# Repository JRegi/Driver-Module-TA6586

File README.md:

# Dual Driver Module with TA6586

## **Description**
A little module with two TA6586 full-bridge drivers, designed to be small while maintaining a decent thermal performance.
The PCB is designed for PCBWay Quick-Turn PCB capabilities.

# 3D view

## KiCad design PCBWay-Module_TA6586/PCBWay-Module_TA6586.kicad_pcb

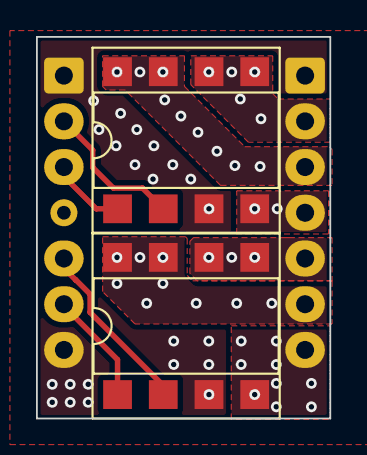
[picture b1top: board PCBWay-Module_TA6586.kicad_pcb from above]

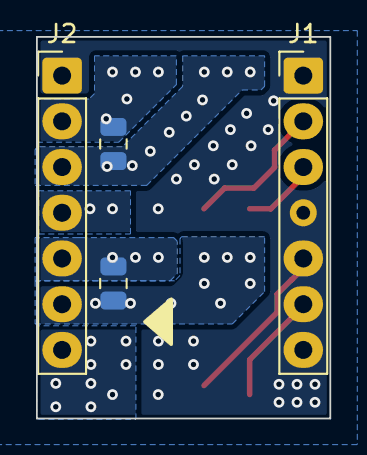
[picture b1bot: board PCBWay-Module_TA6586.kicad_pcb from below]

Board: 2 copper layers, 16.3 x 21.2 mm, 6 parts (4 on the bottom side), 10 nets.

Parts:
C1, C2: 100; C_0805_2012Metric
J1, J2: Conn_01x07_Pin; PinHeader_1x07_P2.54mm_Vertical
U1, U2: DIP-8_W7.62mm_SMDSocket_SmallPads

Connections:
/IN_A1: J1.6, U1.1 (IN1)
/IN_A2: J1.5, U1.2 (IN2)
/IN_B1: J1.3, U2.1 (IN1)
/IN_B2: J1.2, U2.2 (IN2)
/OUT_A1: C2.2, J2.5, U1.5 (OUT1), U1.6 (OUT1)
/OUT_A2: C2.1, J2.6, U1.7 (OUT2), U1.8 (OUT2)
/OUT_B1: C1.2, J2.2, U2.5 (OUT1), U2.6 (OUT1)
/OUT_B2: C1.1, J2.3, U2.7 (OUT2), U2.8 (OUT2)
/VM: J2.4, J2.7, U1.4 (VM), U2.4 (VM)
GND: J1.1, J1.7, J2.1, U1.3 (GND), U2.3 (GND)

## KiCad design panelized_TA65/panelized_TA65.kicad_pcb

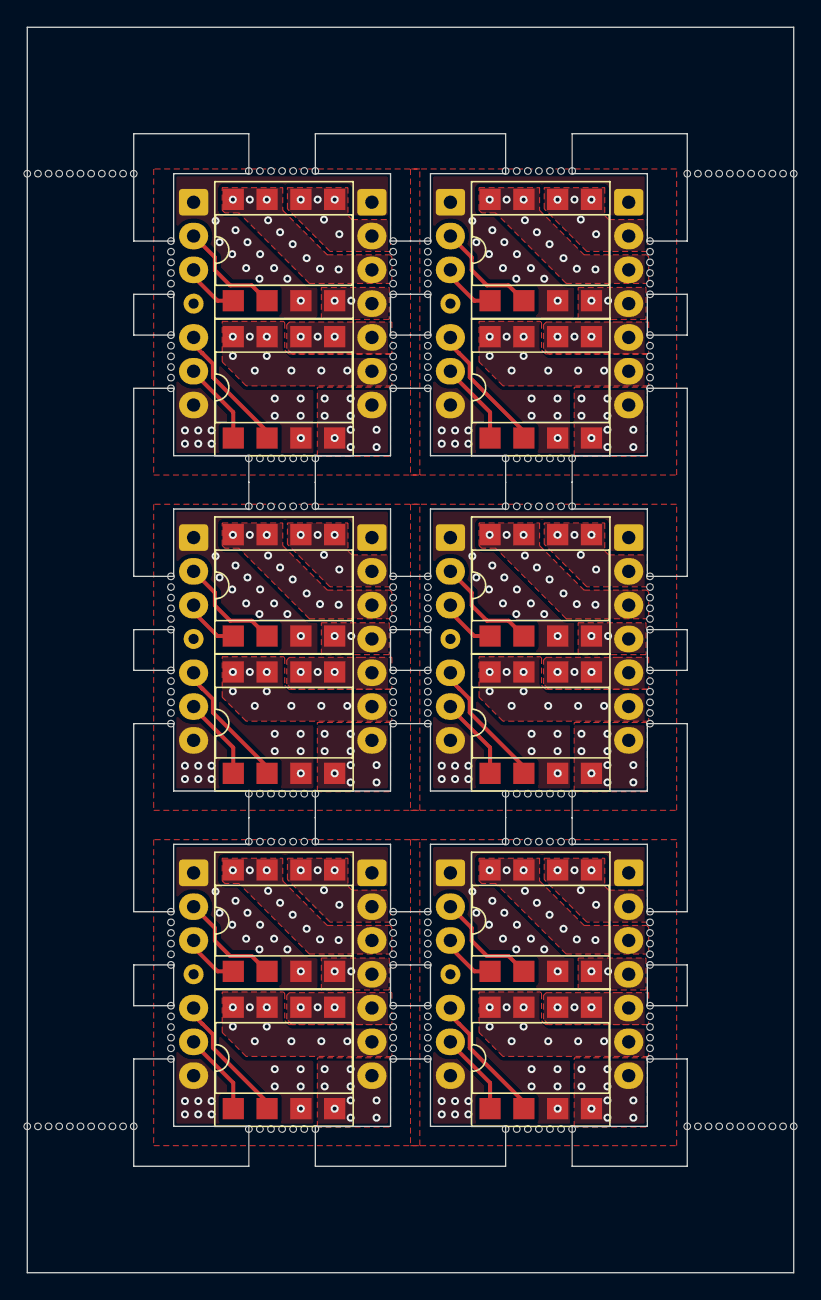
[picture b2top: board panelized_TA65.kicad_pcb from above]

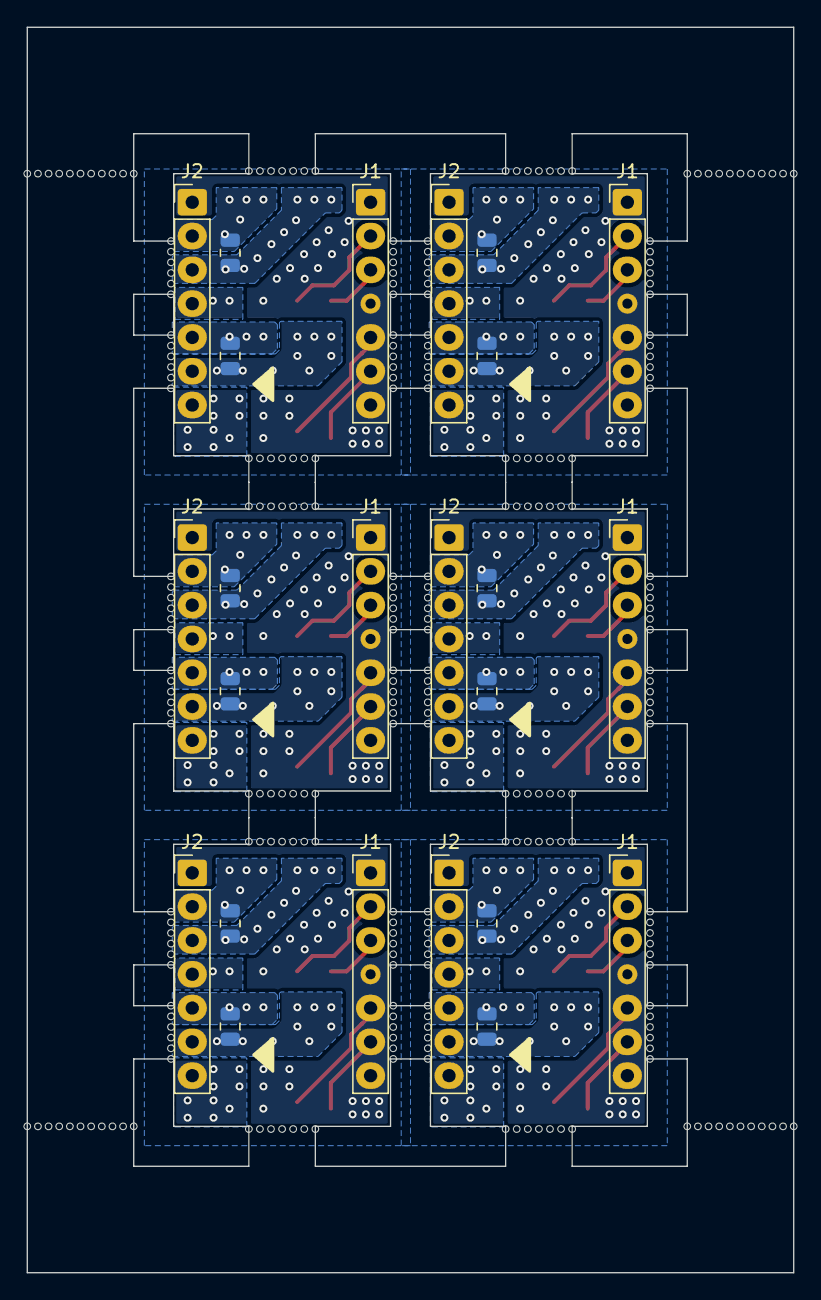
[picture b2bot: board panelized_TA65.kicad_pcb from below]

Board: 2 copper layers, 57.6 x 93.6 mm, 308 parts (24 on the bottom side), 60 nets.

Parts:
C1, C1#2, C1#3, C1#4, C1#5, C1#6, C2, C2#2, C2#3, C2#4, C2#5, C2#6: 100; C_0805_2012Metric
J1, J1#2, J1#3, J1#4, J1#5, J1#6, J2, J2#2, J2#3, J2#4, J2#5, J2#6: Conn_01x07_Pin; PinHeader_1x07_P2.54mm_Vertical
KiKit_MB_1_1, KiKit_MB_1_2, KiKit_MB_1_3, KiKit_MB_1_4, KiKit_MB_1_5, KiKit_MB_1_6, KiKit_MB_2_1, KiKit_MB_2_2, KiKit_MB_2_3, KiKit_MB_2_4, KiKit_MB_2_5, KiKit_MB_2_6, KiKit_MB_3_1, KiKit_MB_3_2, KiKit_MB_3_3, KiKit_MB_3_4, KiKit_MB_3_5, KiKit_MB_3_6, KiKit_MB_4_1, KiKit_MB_4_2, KiKit_MB_4_3, KiKit_MB_4_4, KiKit_MB_4_5, KiKit_MB_4_6, KiKit_MB_5_1, KiKit_MB_5_2, KiKit_MB_5_3, KiKit_MB_5_4, KiKit_MB_5_5, KiKit_MB_5_6, KiKit_MB_5_7, KiKit_MB_6_1, KiKit_MB_6_2, KiKit_MB_6_3, KiKit_MB_6_4, KiKit_MB_6_5, KiKit_MB_6_6, KiKit_MB_6_7, KiKit_MB_7_1, KiKit_MB_7_2, KiKit_MB_7_3, KiKit_MB_7_4, KiKit_MB_7_5, KiKit_MB_7_6, KiKit_MB_8_1, KiKit_MB_8_2, KiKit_MB_8_3, KiKit_MB_8_4, KiKit_MB_8_5, KiKit_MB_8_6, KiKit_MB_9_1, KiKit_MB_9_2, KiKit_MB_9_3, KiKit_MB_9_4, KiKit_MB_9_5, KiKit_MB_9_6, KiKit_MB_10_1, KiKit_MB_10_2, KiKit_MB_10_3, KiKit_MB_10_4, KiKit_MB_10_5, KiKit_MB_10_6, KiKit_MB_11_1, KiKit_MB_11_2, KiKit_MB_11_3, KiKit_MB_11_4, KiKit_MB_11_5, KiKit_MB_11_6, KiKit_MB_11_7, KiKit_MB_12_1, KiKit_MB_12_2, KiKit_MB_12_3, KiKit_MB_12_4, KiKit_MB_12_5, KiKit_MB_12_6, KiKit_MB_12_7, KiKit_MB_13_1, KiKit_MB_13_2, KiKit_MB_13_3, KiKit_MB_13_4, KiKit_MB_13_5, KiKit_MB_13_6, KiKit_MB_14_1, KiKit_MB_14_2, KiKit_MB_14_3, KiKit_MB_14_4, KiKit_MB_14_5, KiKit_MB_14_6, KiKit_MB_15_1, KiKit_MB_15_2, KiKit_MB_15_3, KiKit_MB_15_4, KiKit_MB_15_5, KiKit_MB_15_6, KiKit_MB_16_1, KiKit_MB_16_2, KiKit_MB_16_3, KiKit_MB_16_4, KiKit_MB_16_5, KiKit_MB_16_6, KiKit_MB_17_1, KiKit_MB_17_2, KiKit_MB_17_3, KiKit_MB_17_4, KiKit_MB_17_5, KiKit_MB_17_6, KiKit_MB_17_7, KiKit_MB_18_1, KiKit_MB_18_2, KiKit_MB_18_3, KiKit_MB_18_4, KiKit_MB_18_5, KiKit_MB_18_6, KiKit_MB_18_7, KiKit_MB_19_1, KiKit_MB_19_2, KiKit_MB_19_3, KiKit_MB_19_4, KiKit_MB_19_5, KiKit_MB_19_6, KiKit_MB_20_1, KiKit_MB_20_2, KiKit_MB_20_3, KiKit_MB_20_4, KiKit_MB_20_5, KiKit_MB_20_6, KiKit_MB_21_1, KiKit_MB_21_2, KiKit_MB_21_3, KiKit_MB_21_4, KiKit_MB_21_5, KiKit_MB_21_6, KiKit_MB_22_1, KiKit_MB_22_2, KiKit_MB_22_3, KiKit_MB_22_4, KiKit_MB_22_5, KiKit_MB_22_6, KiKit_MB_23_1, KiKit_MB_23_2, KiKit_MB_23_3, KiKit_MB_23_4, KiKit_MB_23_5, KiKit_MB_23_6, KiKit_MB_23_7, KiKit_MB_24_1, KiKit_MB_24_2, KiKit_MB_24_3, KiKit_MB_24_4, KiKit_MB_24_5, KiKit_MB_24_6, KiKit_MB_24_7, KiKit_MB_25_1, KiKit_MB_25_2, KiKit_MB_25_3, KiKit_MB_25_4, KiKit_MB_25_5, KiKit_MB_25_6, KiKit_MB_26_1, KiKit_MB_26_2, KiKit_MB_26_3, KiKit_MB_26_4, KiKit_MB_26_5, KiKit_MB_26_6, KiKit_MB_27_1, KiKit_MB_27_2, KiKit_MB_27_3, KiKit_MB_27_4, KiKit_MB_27_5, KiKit_MB_27_6, KiKit_MB_28_1, KiKit_MB_28_2, KiKit_MB_28_3, KiKit_MB_28_4, KiKit_MB_28_5, KiKit_MB_28_6, KiKit_MB_29_1, KiKit_MB_29_2, KiKit_MB_29_3, KiKit_MB_29_4, KiKit_MB_29_5, KiKit_MB_29_6, KiKit_MB_29_7, KiKit_MB_30_1, KiKit_MB_30_2, KiKit_MB_30_3, KiKit_MB_30_4, KiKit_MB_30_5, KiKit_MB_30_6, KiKit_MB_30_7, KiKit_MB_31_1, KiKit_MB_31_2, KiKit_MB_31_3, KiKit_MB_31_4, KiKit_MB_31_5, KiKit_MB_31_6, KiKit_MB_32_1, KiKit_MB_32_2, KiKit_MB_32_3, KiKit_MB_32_4, KiKit_MB_32_5, KiKit_MB_32_6, KiKit_MB_33_1, KiKit_MB_33_2, KiKit_MB_33_3, KiKit_MB_33_4, KiKit_MB_33_5, KiKit_MB_33_6, KiKit_MB_34_1, KiKit_MB_34_2, KiKit_MB_34_3, KiKit_MB_34_4, KiKit_MB_34_5, KiKit_MB_34_6, KiKit_MB_35_1, KiKit_MB_35_2, KiKit_MB_35_3, KiKit_MB_35_4, KiKit_MB_35_5, KiKit_MB_35_6, KiKit_MB_35_7, KiKit_MB_36_1, KiKit_MB_36_2, KiKit_MB_36_3, KiKit_MB_36_4, KiKit_MB_36_5, KiKit_MB_36_6, KiKit_MB_36_7, KiKit_MB_37_1, KiKit_MB_37_2, KiKit_MB_37_3, KiKit_MB_37_4, KiKit_MB_37_5, KiKit_MB_37_6, KiKit_MB_37_7, KiKit_MB_37_8, KiKit_MB_37_9, KiKit_MB_37_10, KiKit_MB_37_11, KiKit_MB_38_1, KiKit_MB_38_2, KiKit_MB_38_3, KiKit_MB_38_4, KiKit_MB_38_5, KiKit_MB_38_6, KiKit_MB_38_7, KiKit_MB_38_8, KiKit_MB_38_9, KiKit_MB_38_10, KiKit_MB_38_11, KiKit_MB_39_1, KiKit_MB_39_2, KiKit_MB_39_3, KiKit_MB_39_4, KiKit_MB_39_5, KiKit_MB_39_6, KiKit_MB_39_7, KiKit_MB_39_8, KiKit_MB_39_9, KiKit_MB_39_10, KiKit_MB_39_11, KiKit_MB_40_1, KiKit_MB_40_2, KiKit_MB_40_3, KiKit_MB_40_4, KiKit_MB_40_5, KiKit_MB_40_6, KiKit_MB_40_7, KiKit_MB_40_8, KiKit_MB_40_9, KiKit_MB_40_10, KiKit_MB_40_11: NPTH
U1, U1#2, U1#3, U1#4, U1#5, U1#6, U2, U2#2, U2#3, U2#4, U2#5, U2#6: DIP-8_W7.62mm_SMDSocket_SmallPads

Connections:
Board_0-/IN_A1: J1#6.6, U1#4.1 (IN1)
Board_0-/IN_A2: J1#6.5, U1#4.2 (IN2)
Board_0-/IN_B1: J1#6.3, U2#3.1 (IN1)
Board_0-/IN_B2: J1#6.2, U2#3.2 (IN2)
Board_0-/OUT_A1: C2#3.2, J2.5, U1#4.5 (OUT1), U1#4.6 (OUT1)
Board_0-/OUT_A2: C2#3.1, J2.6, U1#4.7 (OUT2), U1#4.8 (OUT2)
Board_0-/OUT_B1: C1#4.2, J2.2, U2#3.5 (OUT1), U2#3.6 (OUT1)
Board_0-/OUT_B2: C1#4.1, J2.3, U2#3.7 (OUT2), U2#3.8 (OUT2)
Board_0-/VM: J2.4, J2.7, U1#4.4 (VM), U2#3.4 (VM)
Board_0-GND: J1#6.1, J1#6.7, J2.1, U1#4.3 (GND), U2#3.3 (GND)
Board_1-/IN_A1: J1#4.6, U1#3.1 (IN1)
Board_1-/IN_A2: J1#4.5, U1#3.2 (IN2)
Board_1-/IN_B1: J1#4.3, U2.1 (IN1)
Board_1-/IN_B2: J1#4.2, U2.2 (IN2)
Board_1-/OUT_A1: C2#2.2, J2#3.5, U1#3.5 (OUT1), U1#3.6 (OUT1)
Board_1-/OUT_A2: C2#2.1, J2#3.6, U1#3.7 (OUT2), U1#3.8 (OUT2)
Board_1-/OUT_B1: C1#3.2, J2#3.2, U2.5 (OUT1), U2.6 (OUT1)
Board_1-/OUT_B2: C1#3.1, J2#3.3, U2.7 (OUT2), U2.8 (OUT2)
Board_1-/VM: J2#3.4, J2#3.7, U1#3.4 (VM), U2.4 (VM)
Board_1-GND: J1#4.1, J1#4.7, J2#3.1, U1#3.3 (GND), U2.3 (GND)
Board_2-/IN_A1: J1#3.6, U1#5.1 (IN1)
Board_2-/IN_A2: J1#3.5, U1#5.2 (IN2)
Board_2-/IN_B1: J1#3.3, U2#2.1 (IN1)
Board_2-/IN_B2: J1#3.2, U2#2.2 (IN2)
Board_2-/OUT_A1: C2#4.2, J2#5.5, U1#5.5 (OUT1), U1#5.6 (OUT1)
Board_2-/OUT_A2: C2#4.1, J2#5.6, U1#5.7 (OUT2), U1#5.8 (OUT2)
Board_2-/OUT_B1: C1#2.2, J2#5.2, U2#2.5 (OUT1), U2#2.6 (OUT1)
Board_2-/OUT_B2: C1#2.1, J2#5.3, U2#2.7 (OUT2), U2#2.8 (OUT2)
Board_2-/VM: J2#5.4, J2#5.7, U1#5.4 (VM), U2#2.4 (VM)
Board_2-GND: J1#3.1, J1#3.7, J2#5.1, U1#5.3 (GND), U2#2.3 (GND)
Board_3-/IN_A1: J1#5.6, U1#6.1 (IN1)
Board_3-/IN_A2: J1#5.5, U1#6.2 (IN2)
Board_3-/IN_B1: J1#5.3, U2#5.1 (IN1)
Board_3-/IN_B2: J1#5.2, U2#5.2 (IN2)
Board_3-/OUT_A1: C2#5.2, J2#6.5, U1#6.5 (OUT1), U1#6.6 (OUT1)
Board_3-/OUT_A2: C2#5.1, J2#6.6, U1#6.7 (OUT2), U1#6.8 (OUT2)
Board_3-/OUT_B1: C1#6.2, J2#6.2, U2#5.5 (OUT1), U2#5.6 (OUT1)
Board_3-/OUT_B2: C1#6.1, J2#6.3, U2#5.7 (OUT2), U2#5.8 (OUT2)
Board_3-/VM: J2#6.4, J2#6.7, U1#6.4 (VM), U2#5.4 (VM)
Board_3-GND: J1#5.1, J1#5.7, J2#6.1, U1#6.3 (GND), U2#5.3 (GND)
Board_4-/IN_A1: J1.6, U1.1 (IN1)
Board_4-/IN_A2: J1.5, U1.2 (IN2)
Board_4-/IN_B1: J1.3, U2#6.1 (IN1)
Board_4-/IN_B2: J1.2, U2#6.2 (IN2)
Board_4-/OUT_A1: C2#6.2, J2#4.5, U1.5 (OUT1), U1.6 (OUT1)
Board_4-/OUT_A2: C2#6.1, J2#4.6, U1.7 (OUT2), U1.8 (OUT2)
Board_4-/OUT_B1: C1.2, J2#4.2, U2#6.5 (OUT1), U2#6.6 (OUT1)
Board_4-/OUT_B2: C1.1, J2#4.3, U2#6.7 (OUT2), U2#6.8 (OUT2)
Board_4-/VM: J2#4.4, J2#4.7, U1.4 (VM), U2#6.4 (VM)
Board_4-GND: J1.1, J1.7, J2#4.1, U1.3 (GND), U2#6.3 (GND)
Board_5-/IN_A1: J1#2.6, U1#2.1 (IN1)
Board_5-/IN_A2: J1#2.5, U1#2.2 (IN2)
Board_5-/IN_B1: J1#2.3, U2#4.1 (IN1)
Board_5-/IN_B2: J1#2.2, U2#4.2 (IN2)
Board_5-/OUT_A1: C2.2, J2#2.5, U1#2.5 (OUT1), U1#2.6 (OUT1)
Board_5-/OUT_A2: C2.1, J2#2.6, U1#2.7 (OUT2), U1#2.8 (OUT2)
Board_5-/OUT_B1: C1#5.2, J2#2.2, U2#4.5 (OUT1), U2#4.6 (OUT1)
Board_5-/OUT_B2: C1#5.1, J2#2.3, U2#4.7 (OUT2), U2#4.8 (OUT2)
Board_5-/VM: J2#2.4, J2#2.7, U1#2.4 (VM), U2#4.4 (VM)
Board_5-GND: J1#2.1, J1#2.7, J2#2.1, U1#2.3 (GND), U2#4.3 (GND)

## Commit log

2024-09-08 PCBWay-module
2024-09-08 the whole thing
2024-09-09 Fixed pinheaders hole size
2024-09-09 Fixed vias
2024-09-15 Added capacitors
2024-09-15 Modified capacitors value
2024-09-16 gerbers
2024-09-16 panels
2024-09-16 panels again
2024-09-19 regenerated gerber files
